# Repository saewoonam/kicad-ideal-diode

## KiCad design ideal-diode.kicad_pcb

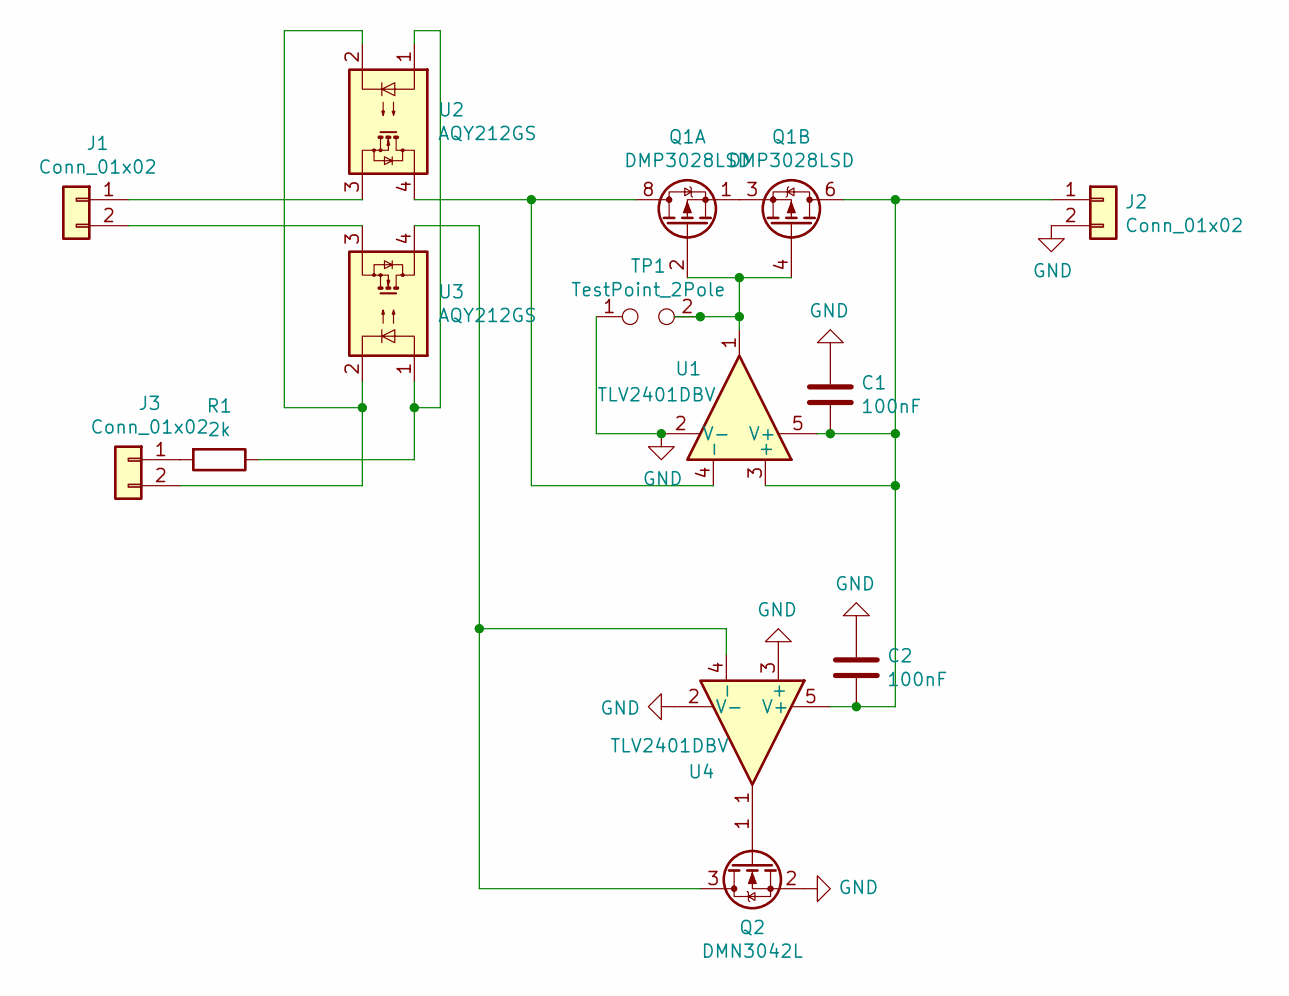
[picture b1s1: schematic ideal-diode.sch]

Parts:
C1, C2: 100nF; C_0603_1608Metric_Pad1.05x0.95mm_HandSolder; MPN CC0603KRX7R9BB104; LCSC C14663
J1, J2, J3: Conn_01x02; JST_PH_B2B-PH-K_1x02_P2.00mm_Vertical
Q1: DMP3028LSD; SO-8_3.9x4.9mm_P1.27mm; MPN DMP3028LSD-13; LCSC C397949
Q2: DMN3042L; SOT-23; MPN DMN3042L-7; LCSC C102621
R1: 2k; R_0603_1608Metric_Pad1.05x0.95mm_HandSolder; MPN 0603WAF2001T5E; LCSC C22975
TP1: TestPoint_2Pole; TestPoint_2Pads_Pitch2.54mm_Drill0.8mm
U1, U4: TLV2401DBV; SOT-23-5; MPN TLV2401DBV; LCSC C202319
U2, U3: AQY212GS; SOP-4_3.8x4.1mm_P2.54mm; LCSC C129283

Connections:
GND: C1.1, C2.1, J2.2, Q2.2 (S), TP1.1, U1.2 (V-), U4.2 (V-), U4.3 (+)
unnamed: C1.2, C2.2, J2.1, Q1.5 (D2), Q1.6 (D2), U1.3 (+), U1.5 (V+), U4.5 (V+)
unnamed: J1.1, U2.3
unnamed: J1.2, U3.3
unnamed: J3.1, R1.2
unnamed: J3.2, U2.2, U3.2
unnamed: Q1.1 (S1), Q1.3 (S2)
unnamed: Q1.2 (G1), Q1.4 (G2), TP1.2, U1.1
unnamed: Q1.7 (D1), Q1.8 (D1), U1.4 (-), U2.4
unnamed: Q2.1 (G), U4.1
unnamed: Q2.3 (D), U3.4, U4.4 (-)
unnamed: R1.1, U2.1, U3.1

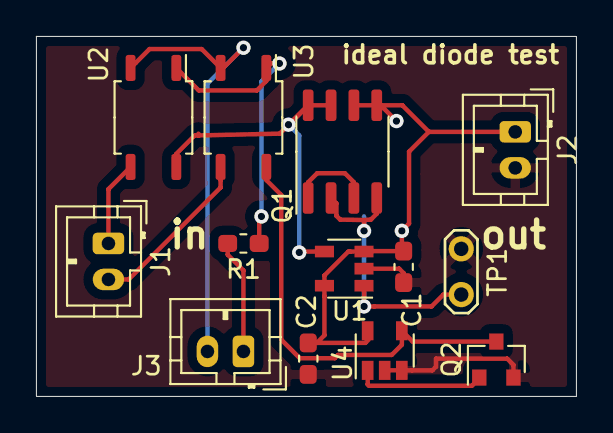
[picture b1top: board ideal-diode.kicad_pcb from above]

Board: 2 copper layers, 30.0 x 20.0 mm, 13 parts (0 on the bottom side), 12 nets.

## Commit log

2021-02-14 add files
2021-02-14 add github action stuff
2021-02-14 add js programs
2021-02-14 Add gh-pages publishing
2021-02-14 Use JamesIves/github-pages-deploy-action@4.0.0 for publishing gh-paages
2021-02-14 tweak to deploy web folder
2021-02-14 Add backup to web
2021-02-14 Deploying to gh-pages from @ saewoonam/kicad-ideal-diode@ab9abb8dad9d2558581087839fe74c92ca795c24 🚀
2021-02-14 update to see if GITHUB_ACTIONS stuff is there
2021-02-14 Use process.env valaue for repository to build url
2021-02-14 User master instead of main... need to figure out branch name
2021-02-14 update on push to master or main
2021-02-14 do on all push... infinite loop is avoided by using github access token by defaault
2021-02-14 get branch name from GITHUB_REF
2021-02-14 Try to push a generated file
2021-02-14 generated
2021-02-14 remove node_modules
2021-02-14 ignore node_modules
2021-02-14 try to remove node_modules again
2021-02-14 Update gitignore
2021-02-14 push only generated
2021-02-14 update generated
2021-02-14 refactor index.js
2021-02-14 build html
2021-02-14 Try to write web/index2.html
2021-02-14 Deploying to gh-pages from @ saewoonam/kicad-ideal-diode@3f3d6f1123c96c87a8279a9a5d5f8e3ebd2e164c 🚀
2021-02-14 Update github action to just do a commit, no add
2021-02-14 tweak github action to update only index.html
2021-02-14 Deploying to gh-pages from @ saewoonam/kicad-ideal-diode@3de71229f3a097f08cf2a9f98eef16ccdd8f4fd1 🚀
2021-02-15 tweak package.json
2021-02-15 remove package.json... not needed
2021-02-15 Eliminate yarn install, fix typo
2021-02-15 rename learn.yml to write_web.yml
2021-02-15 update web_write
2021-02-15 add issue github action
